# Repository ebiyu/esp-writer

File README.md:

# esp-writer

ESP32・ESP8266にコードを書き込むためのライタ回路です。

RTS/DTRによる自動リセット機能が実装されています。

## 使用部品

秋月電子のUSBシリアルモジュールを活用しています。

https://akizukidenshi.com/catalog/g/gK-06693/

## ピン配置

書き込みには6ピンを利用します。

1. EN
2. RXD
3. TXD
4. (none)
5. BOOT
6. GND

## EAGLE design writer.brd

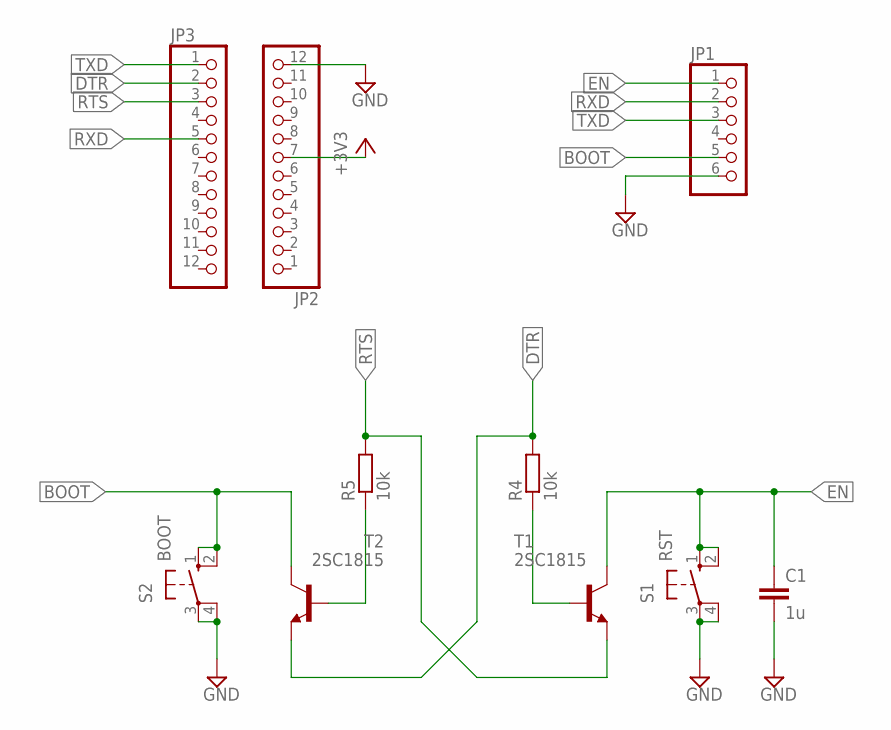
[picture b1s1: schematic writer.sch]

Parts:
C1: 1u; C050-025X075
JP1: PINHD-1X6; 1X06
JP2, JP3: PINHD-1X12; 1X12
R4, R5: 10k; 0207/10
S1: RST; B3F-10XX
S2: BOOT; B3F-10XX
T1, T2: 2SC1815; TO92-ECB

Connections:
+3V3: JP2.7
BOOT: JP1.5, S2.1 (S), S2.2 (S1), T2.C
DTR: JP3.2, R4.2, T2.E
EN: C1.1, JP1.1, S1.1 (S), S1.2 (S1), T1.C
GND: C1.2, JP1.6, JP2.12, S1.3, S1.4 (P1), S2.3, S2.4 (P1)
unnamed: R5.1, T2.B
unnamed: R4.1, T1.B
RTS: JP3.3, R5.2, T1.E
RXD: JP1.2, JP3.5
TXD: JP1.3, JP3.1

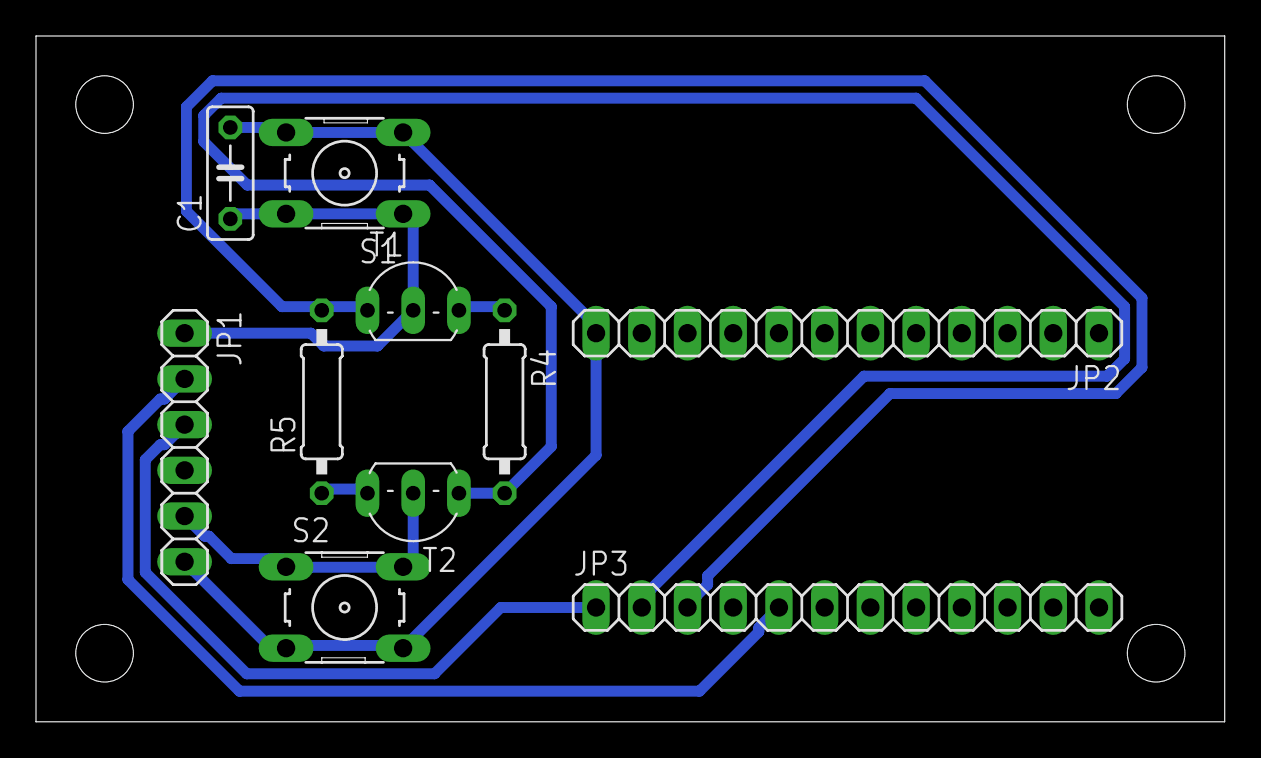
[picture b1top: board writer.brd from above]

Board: 2 copper layers, 66.0 x 38.1 mm, 10 parts (0 on the bottom side), 9 nets.

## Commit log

2021-04-02 init
2021-04-02 feat: designed writer
2021-04-08 feat: remove unnecessary resister & adjust layout
2021-04-08 doc: write readme
